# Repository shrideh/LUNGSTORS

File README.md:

**Full project presentation available at: https://protors.co/lungstors/**

# LUNGSTORS
**Blower based Open Source Medical Ventilator**

<p align="center">

</p>

## License
Copyright (C) 2020 PROTORS  <info@protors.co>

Licensed under CERN-OHL-P version 2

You may redistribute and modify this documentation and make products
using it under the terms of the [CERN-OHL-P v2](https://ohwr.org/project/cernohl/wikis/Documents/CERN-OHL-version-2).
This documentation is distributed WITHOUT ANY EXPRESS OR IMPLIED
WARRANTY, INCLUDING OF MERCHANTABILITY, SATISFACTORY QUALITY
AND FITNESS FOR A PARTICULAR PURPOSE. Please see the CERN-OHL-P v2
for applicable conditions.

For more information view [LICENSE.txt](./LICENSE.txt) file.

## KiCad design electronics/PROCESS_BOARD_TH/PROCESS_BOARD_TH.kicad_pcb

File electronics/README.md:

**Full project presentation available at: https://protors.co/lungstors/**
# PROCESS BOARD
The *KiCad* projects of the printed circuit boards for process control are available in subfolders.

## PROCESS BOARD SMD
In folder `PROCESS_BOARD_SMD` a surface-mount device (SMD) version is available.

## PROCESS BOARD TH
In folder `PROCESS_BOARD_TH` a through-hole (TH) version is available.

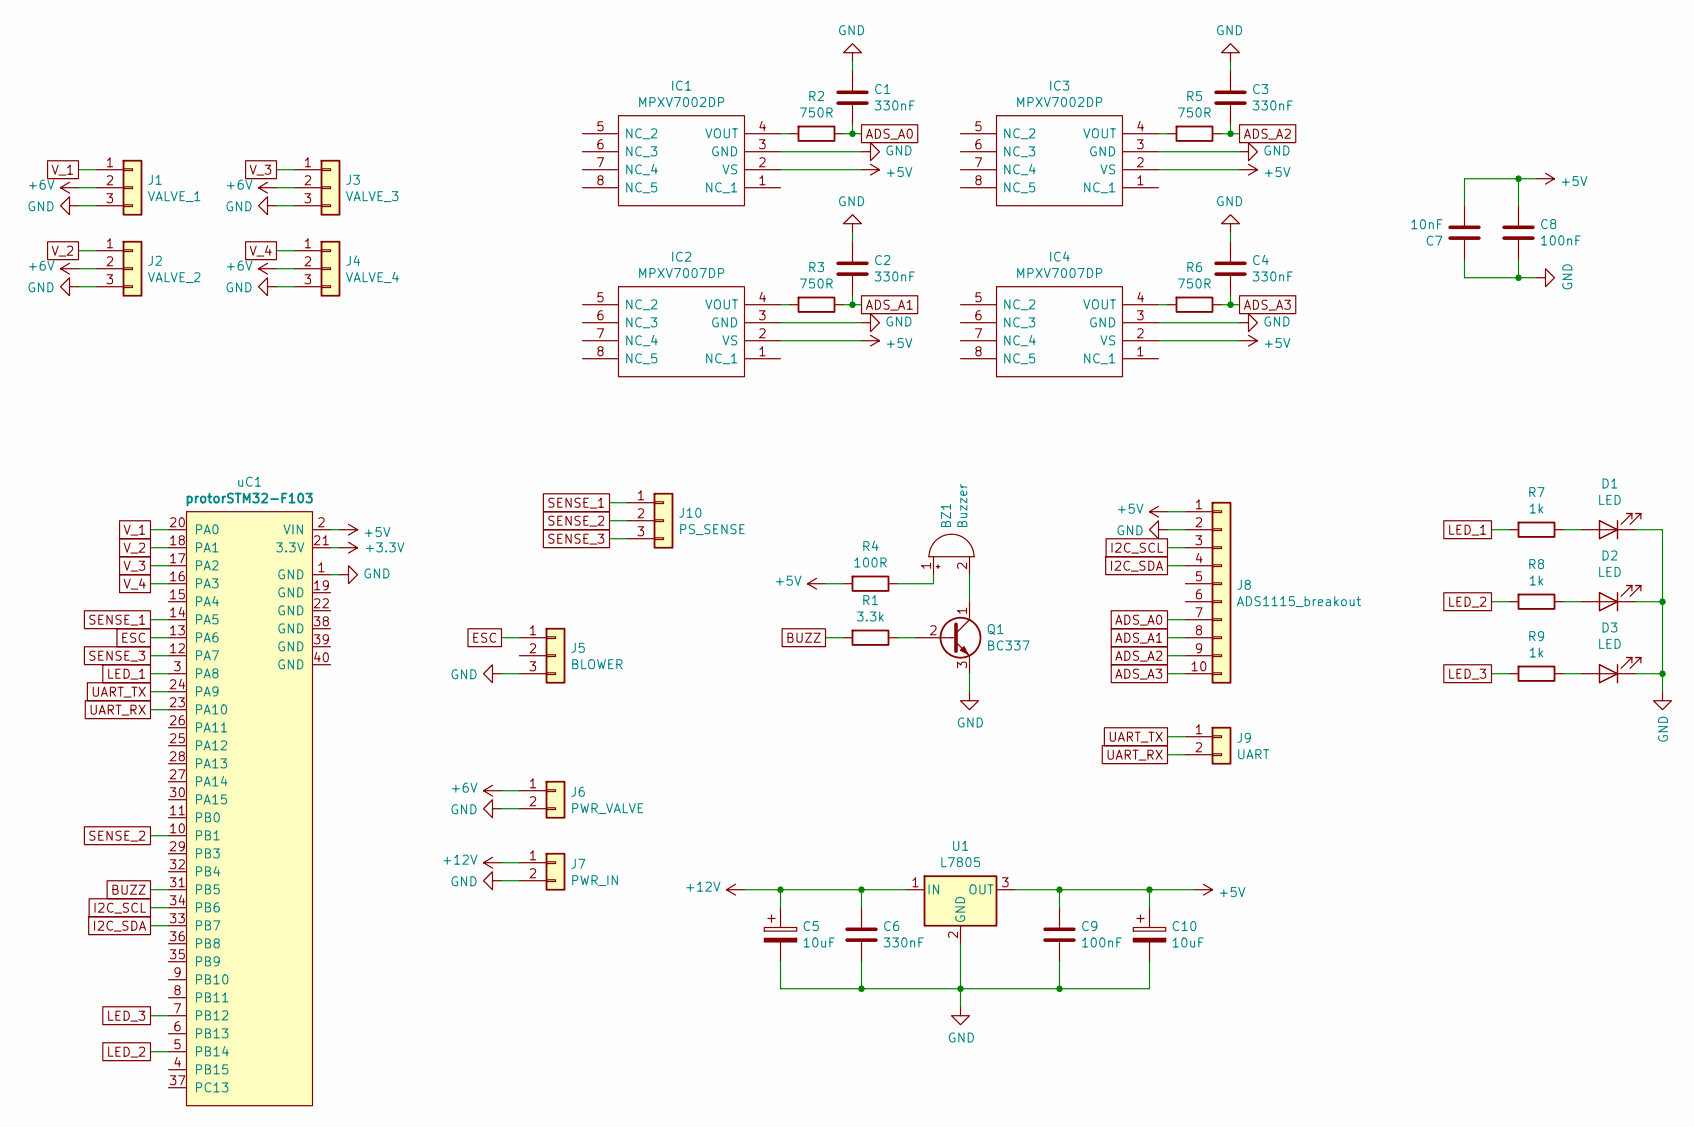
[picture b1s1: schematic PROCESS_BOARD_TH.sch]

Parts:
BZ1: Buzzer; Buzzer_12x9.5RM7.6
C1, C2, C3, C4, C6: 330nF; C_Rect_L7.0mm_W4.5mm_P5.00mm
C5, C10: 10uF; CP_Radial_D5.0mm_P2.50mm
C7: 10nF; C_Rect_L7.0mm_W2.0mm_P5.00mm
C8, C9: 100nF; C_Rect_L7.0mm_W2.5mm_P5.00mm
D1, D2, D3: LED; LED_D5.0mm
IC1, IC3: MPXV7002DP; MPXV7002DPT1
IC2, IC4: MPXV7007DP; MPXV7002DPT1
J1: VALVE_1; PinHeader_1x03_P2.54mm_Vertical
J2: VALVE_2; PinHeader_1x03_P2.54mm_Vertical
J3: VALVE_3; PinHeader_1x03_P2.54mm_Vertical
J4: VALVE_4; PinHeader_1x03_P2.54mm_Vertical
J5: BLOWER; PinHeader_1x03_P2.54mm_Vertical
J6: PWR_VALVE; TerminalBlock_bornier-2_P5.08mm
J7: PWR_IN; TerminalBlock_bornier-2_P5.08mm
J8: ADS1115_breakout; PinSocket_1x10_P2.54mm_Vertical
J9: UART; TerminalBlock_bornier-2_P5.08mm
J10: PS_SENSE; TerminalBlock_bornier-3_P5.08mm
Q1: BC337; TO-92L_Inline_Wide
R1: 3.3k; R_Axial_DIN0207_L6.3mm_D2.5mm_P10.16mm_Horizontal
R2, R3, R5, R6: 750R; R_Axial_DIN0207_L6.3mm_D2.5mm_P10.16mm_Horizontal
R4: 100R; R_Axial_DIN0207_L6.3mm_D2.5mm_P10.16mm_Horizontal
R7, R8, R9: 1k; R_Axial_DIN0207_L6.3mm_D2.5mm_P10.16mm_Horizontal
U1: L7805; TO-220-3_Vertical
uC1: protorSTM32-F103; protorSTM32-F103v1.1

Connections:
+5V: C7.2, C8.1, C9.1, C10.1, IC1.2 (VS), IC2.2 (VS), IC3.2 (VS), IC4.2 (VS), J8.1, R4.2, U1.3 (OUT), uC1.2 (VIN)
+6V: J1.2, J2.2, J3.2, J4.2, J6.1
+12V: C5.1, C6.1, J7.1, U1.1 (IN)
ADS_A0: C1.2, J8.7, R2.1
ADS_A1: C2.2, J8.8, R3.1
ADS_A2: C3.2, J8.9, R5.1
ADS_A3: C4.2, J8.10, R6.1
BUZZ: R1.2, uC1.31 (PB5)
ESC: J5.1, uC1.13 (PA6)
GND: C1.1, C2.1, C3.1, C4.1, C5.2, C6.2, C7.1, C8.2, C9.2, C10.2, D1.1 (K), D2.1 (K), D3.1 (K), IC1.3 (GND), IC2.3 (GND), IC3.3 (GND), IC4.3 (GND), J1.3, J2.3, J3.3, J4.3, J5.3, J6.2, J7.2, J8.2, Q1.3 (E), U1.2 (GND), uC1.1 (GND)
I2C_SCL: J8.3, uC1.34 (PB6)
I2C_SDA: J8.4, uC1.33 (PB7)
LED_1: R7.2, uC1.3 (PA8)
LED_2: R8.2, uC1.5 (PB14)
LED_3: R9.2, uC1.7 (PB12)
unnamed: BZ1.1 (-), R4.1
unnamed: BZ1.2 (+), Q1.1 (C)
unnamed: D1.2 (A), R7.1
unnamed: D2.2 (A), R8.1
unnamed: D3.2 (A), R9.1
unnamed: IC1.4 (VOUT), R2.2
unnamed: IC2.4 (VOUT), R3.2
unnamed: IC3.4 (VOUT), R5.2
unnamed: IC4.4 (VOUT), R6.2
unnamed: Q1.2 (B), R1.1
SENSE_1: J10.1, uC1.14 (PA5)
SENSE_2: J10.2, uC1.10 (PB1)
SENSE_3: J10.3, uC1.12 (PA7)
UART_RX: J9.2, uC1.23 (PA10)
UART_TX: J9.1, uC1.24 (PA9)
V_1: J1.1, uC1.20 (PA0)
V_2: J2.1, uC1.18 (PA1)
V_3: J3.1, uC1.17 (PA2)
V_4: J4.1, uC1.16 (PA3)

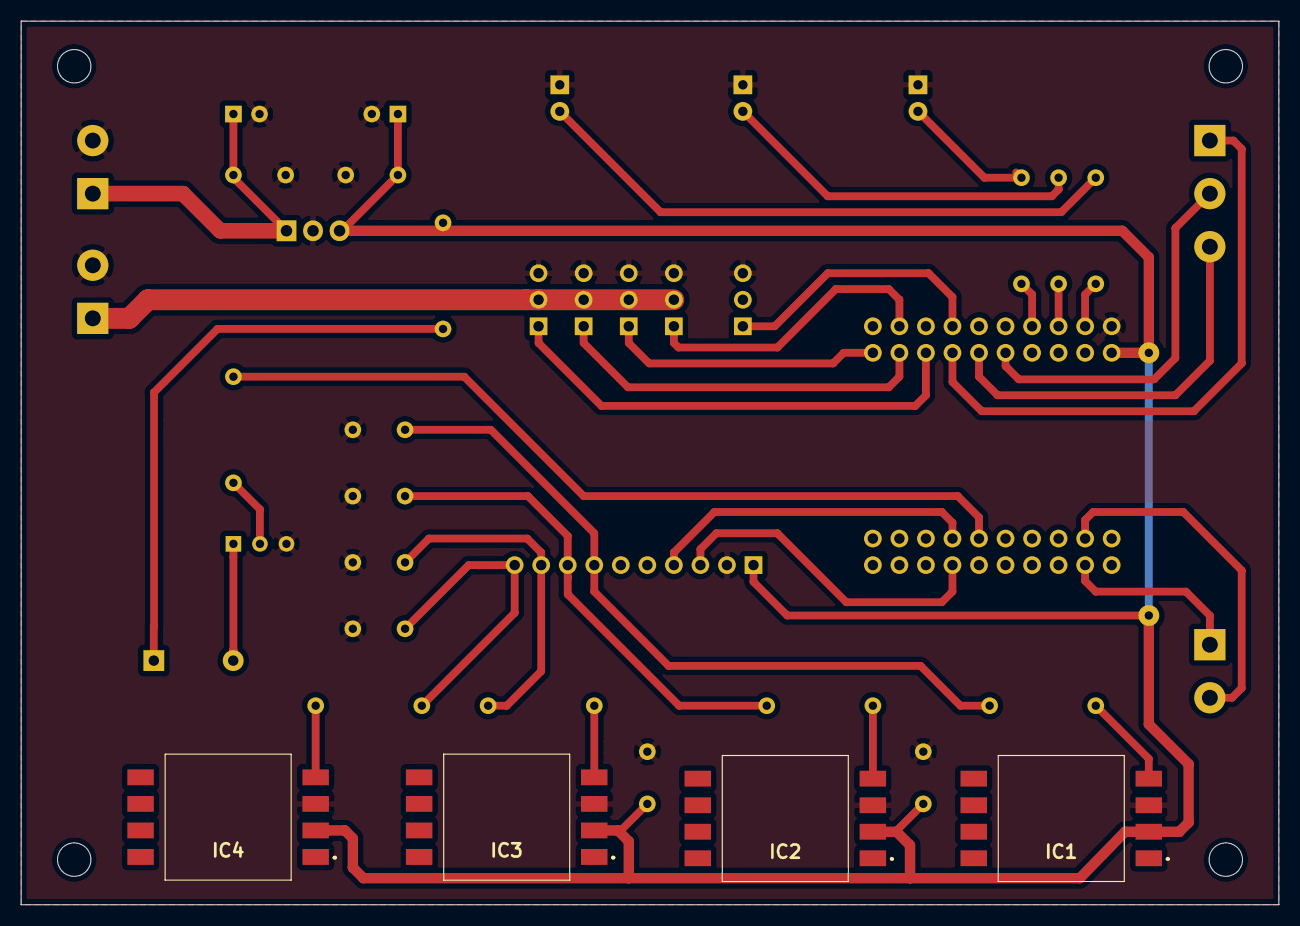
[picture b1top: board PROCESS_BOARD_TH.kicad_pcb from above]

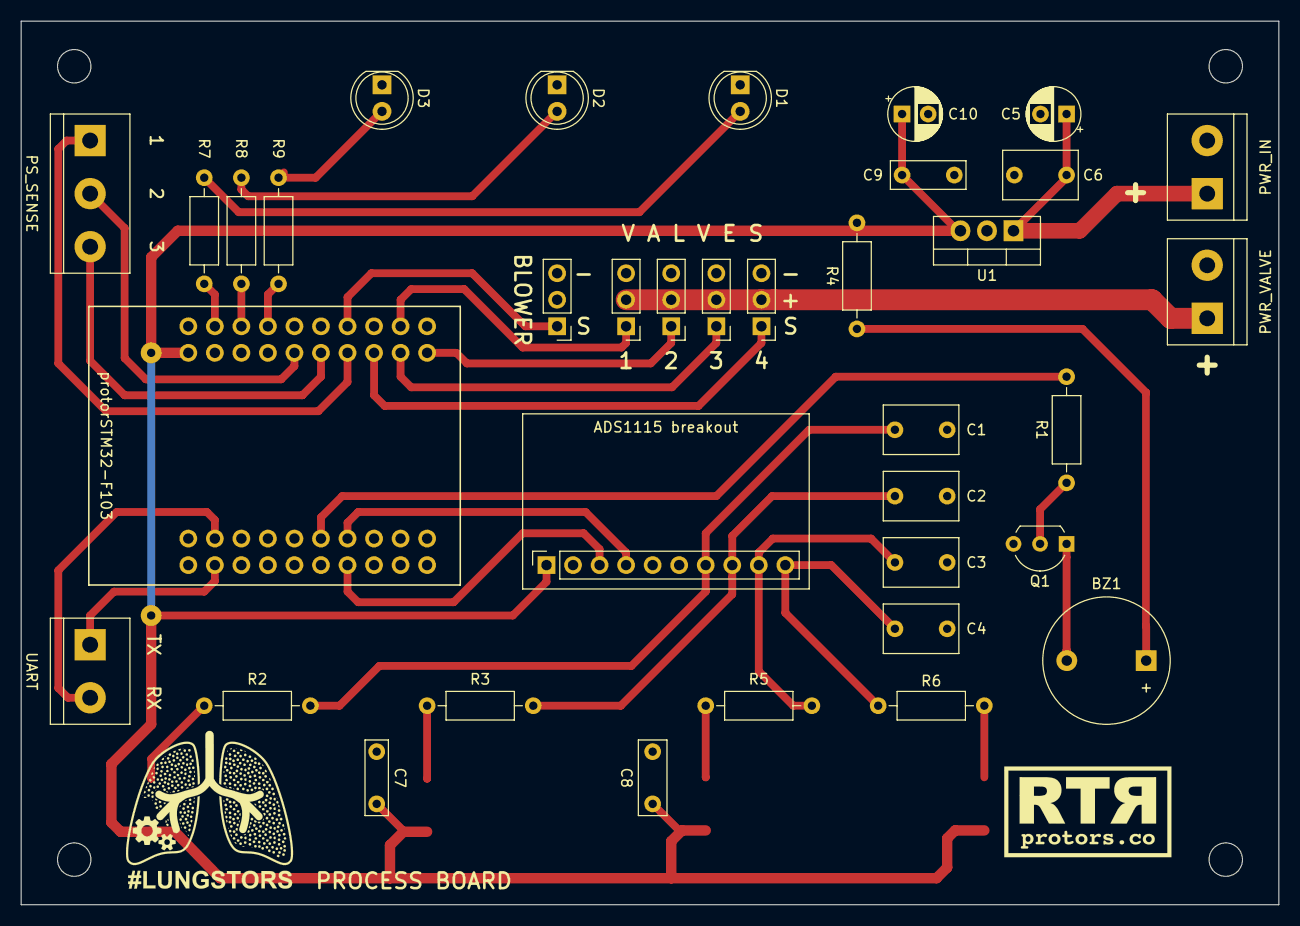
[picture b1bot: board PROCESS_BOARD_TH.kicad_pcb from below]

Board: 2 copper layers, 120.4 x 84.6 mm, 40 parts (36 on the bottom side), 34 nets.

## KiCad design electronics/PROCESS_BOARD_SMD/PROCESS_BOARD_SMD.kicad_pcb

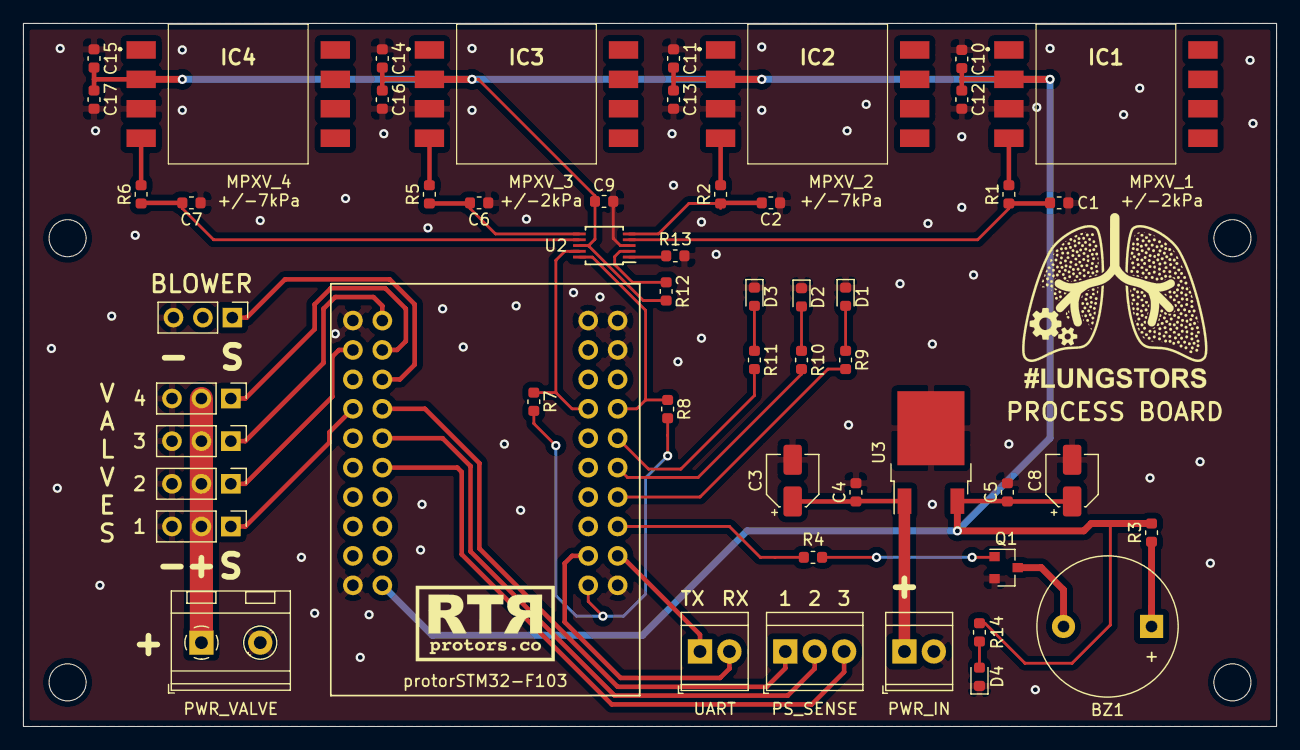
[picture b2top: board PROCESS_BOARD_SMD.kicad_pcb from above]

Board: 2 copper layers, 108.2 x 60.7 mm, 53 parts (0 on the bottom side), 38 nets.

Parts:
BZ1: Buzzer; Buzzer_12x9.5RM7.6
C1, C2, C4, C6, C7: 330nF; C_0603_1608Metric
C3: 10uF; CP_Elec_4x4.5
C5, C12, C13, C16, C17: 100nF; C_0603_1608Metric
C8: 10uF; CP_Elec_4x5.4
C9: 1uF; C_0603_1608Metric
C10, C11, C14, C15: 10nF; C_0603_1608Metric
D1, D2, D3, D4: LED; LED_0603_1608Metric
IC1, IC3: MPXV7002DP; MPXV7002DPT1
IC2, IC4: MPXV7007DP; MPXV7002DPT1
J1: VALVE_1; PinHeader_1x03_P2.54mm_Vertical
J2: VALVE_2; PinHeader_1x03_P2.54mm_Vertical
J3: VALVE_3; PinHeader_1x03_P2.54mm_Vertical
J4: VALVE_4; PinHeader_1x03_P2.54mm_Vertical
J5: COMPRESSOR; PinHeader_1x03_P2.54mm_Vertical
J6: PWR_VALVE; TerminalBlock_RND_205-00232_1x02_P5.08mm_Horizontal
J7: PWR_IN; TerminalBlock_TE_282834-2_1x02_P2.54mm_Horizontal
J8: PS_SENSE; TerminalBlock_TE_282834-3_1x03_P2.54mm_Horizontal
J9: UART; TerminalBlock_TE_282834-2_1x02_P2.54mm_Horizontal
Q1: BC817; SOT-23
R1, R2, R5, R6: 750R; R_0603_1608Metric
R3: 100R; R_0603_1608Metric
R4: 3.3k; R_0603_1608Metric
R7, R8, R12, R13: 10k; R_0603_1608Metric
R9, R10, R11, R14: 1k; R_0603_1608Metric
U2: ADS1115IDGS; TSSOP-10_3x3mm_P0.5mm
U3: LM78M05_TO252; TO-252-2
uC1: protorSTM32-F103; protorSTM32-F103v1.1

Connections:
+3V3: R7.2, R8.2, uC1.21
+5V: C5.1, C8.1, C9.2, C10.2, C11.2, C12.1, C13.1, C14.2, C15.2, C16.1, C17.1, IC1.2, IC2.2, IC3.2, IC4.2, R3.2, R12.2, R14.2, U2.8, U3.3, uC1.2
+6V: J1.2, J2.2, J3.2, J4.2, J6.1
+12V: C3.1, C4.1, J7.1, U3.1
ADS_A0: C1.2, R1.1, U2.4
ADS_A1: C2.2, R2.1, U2.5
ADS_A2: C6.2, R5.1, U2.6
ADS_A3: C7.2, R6.1, U2.7
BUZZ: R4.2, uC1.26
ESC: J5.1, uC1.16
GND: C1.1, C2.1, C3.2, C4.2, C5.2, C6.1, C7.1, C8.2, C9.1, C10.1, C11.1, C12.2, C13.2, C14.1, C15.1, C16.2, C17.2, D1.1, D2.1, D3.1, D4.1, IC1.3, IC2.3, IC3.3, IC4.3, J1.3, J2.3, J3.3, J4.3, J5.3, J6.2, J7.2, Q1.2, R13.2, U2.3, U3.2, uC1.1, uC1.19, uC1.22, uC1.38, uC1.39, uC1.40
I2C_SCL: R8.1, U2.10, uC1.34
I2C_SDA: R7.1, U2.9, uC1.33
LED_1: R9.2, uC1.28
LED_2: R10.2, uC1.30
LED_3: R11.2, uC1.32
unnamed: BZ1.1, R3.1
unnamed: BZ1.2, Q1.3
unnamed: D1.2, R9.1
unnamed: D2.2, R10.1
unnamed: D3.2, R11.1
unnamed: D4.2, R14.1
unnamed: IC1.4, R1.2
unnamed: IC2.4, R2.2
unnamed: IC3.4, R5.2
unnamed: IC4.4, R6.2
unnamed: Q1.1, R4.1
unnamed: R12.1, U2.2
unnamed: R13.1, U2.1
SENSE_1: J8.1, uC1.14
SENSE_2: J8.2, uC1.12
SENSE_3: J8.3, uC1.10
UART_RX: J9.2, uC1.23
UART_TX: J9.1, uC1.24
V_1: J1.1, uC1.13
V_2: J2.1, uC1.17
V_3: J3.1, uC1.20
V_4: J4.1, uC1.18

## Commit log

2020-05-02 Add PROCESS BOARD
2020-05-02 Add images
2020-05-02 Add models
2020-05-06 logo upload
2020-05-06 labels added
